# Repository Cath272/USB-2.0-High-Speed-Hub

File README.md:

# USB-2.0-High-Speed-Hub
USB 2.0 High Speed Hub with MicroSD card slot PCB designed with Kicad 8.0

Kicad Project Files, Gerber Files and STL for the case can be found in the project folders
Case uses M2X6 Screws 

# ICs

### CH334

  - USB2.0 protocol compliant 4-port USB HUB controller chip

  - Uses a 12MHz Crystal

  - 0603 100mA Fuse for limiting power to ic

  - Internal 5V to 3.3V LDO

  - Activity LED

  - [Datasheet](https://www.wch-ic.com/downloads/CH334DS1_PDF.html)

### GL823K 

  - USB 2.0 SD/MSPRO Card Reader Controller

  - Internal 5V to 3.3V LDO, can self power microSD card

  - Activity LED
  
  - [Datasheet](https://www.lcsc.com/datasheet/lcsc_datasheet_2409272232_Genesys-Logic-GL823K-HCY04_C284879.pdf)

### CH213K
  - 0.5A Low dropout ideal diode chip with current limiting function 

  - [Datasheet](https://www.wch-ic.com/downloads/CH213DS1_PDF.html)

### USBLC6
- Very low capacitance ESD protection for USB data lines

- [Datasheet](https://www.st.com/resource/en/datasheet/usblc6-2.pdf)

# Ports

### UPSTREAM

- 1 USB Type C Upstream Port (16P SMD PORT)

### DOWNSTREAM

- 2 USB TYPE C Downstream Ports (16P SMD PORT)

- 1 USB Type A Downstream Port (AF10.0 USB A, the footprint is wrong so i bent the front legs when I assambled it, to be changed) 

- 1 MicroSD card Slot (Common style size 14*15mm)

USB C ports are USB PD compliant

# Schematic

# PCB

FRONT:

BACK:

3D:

# Photos

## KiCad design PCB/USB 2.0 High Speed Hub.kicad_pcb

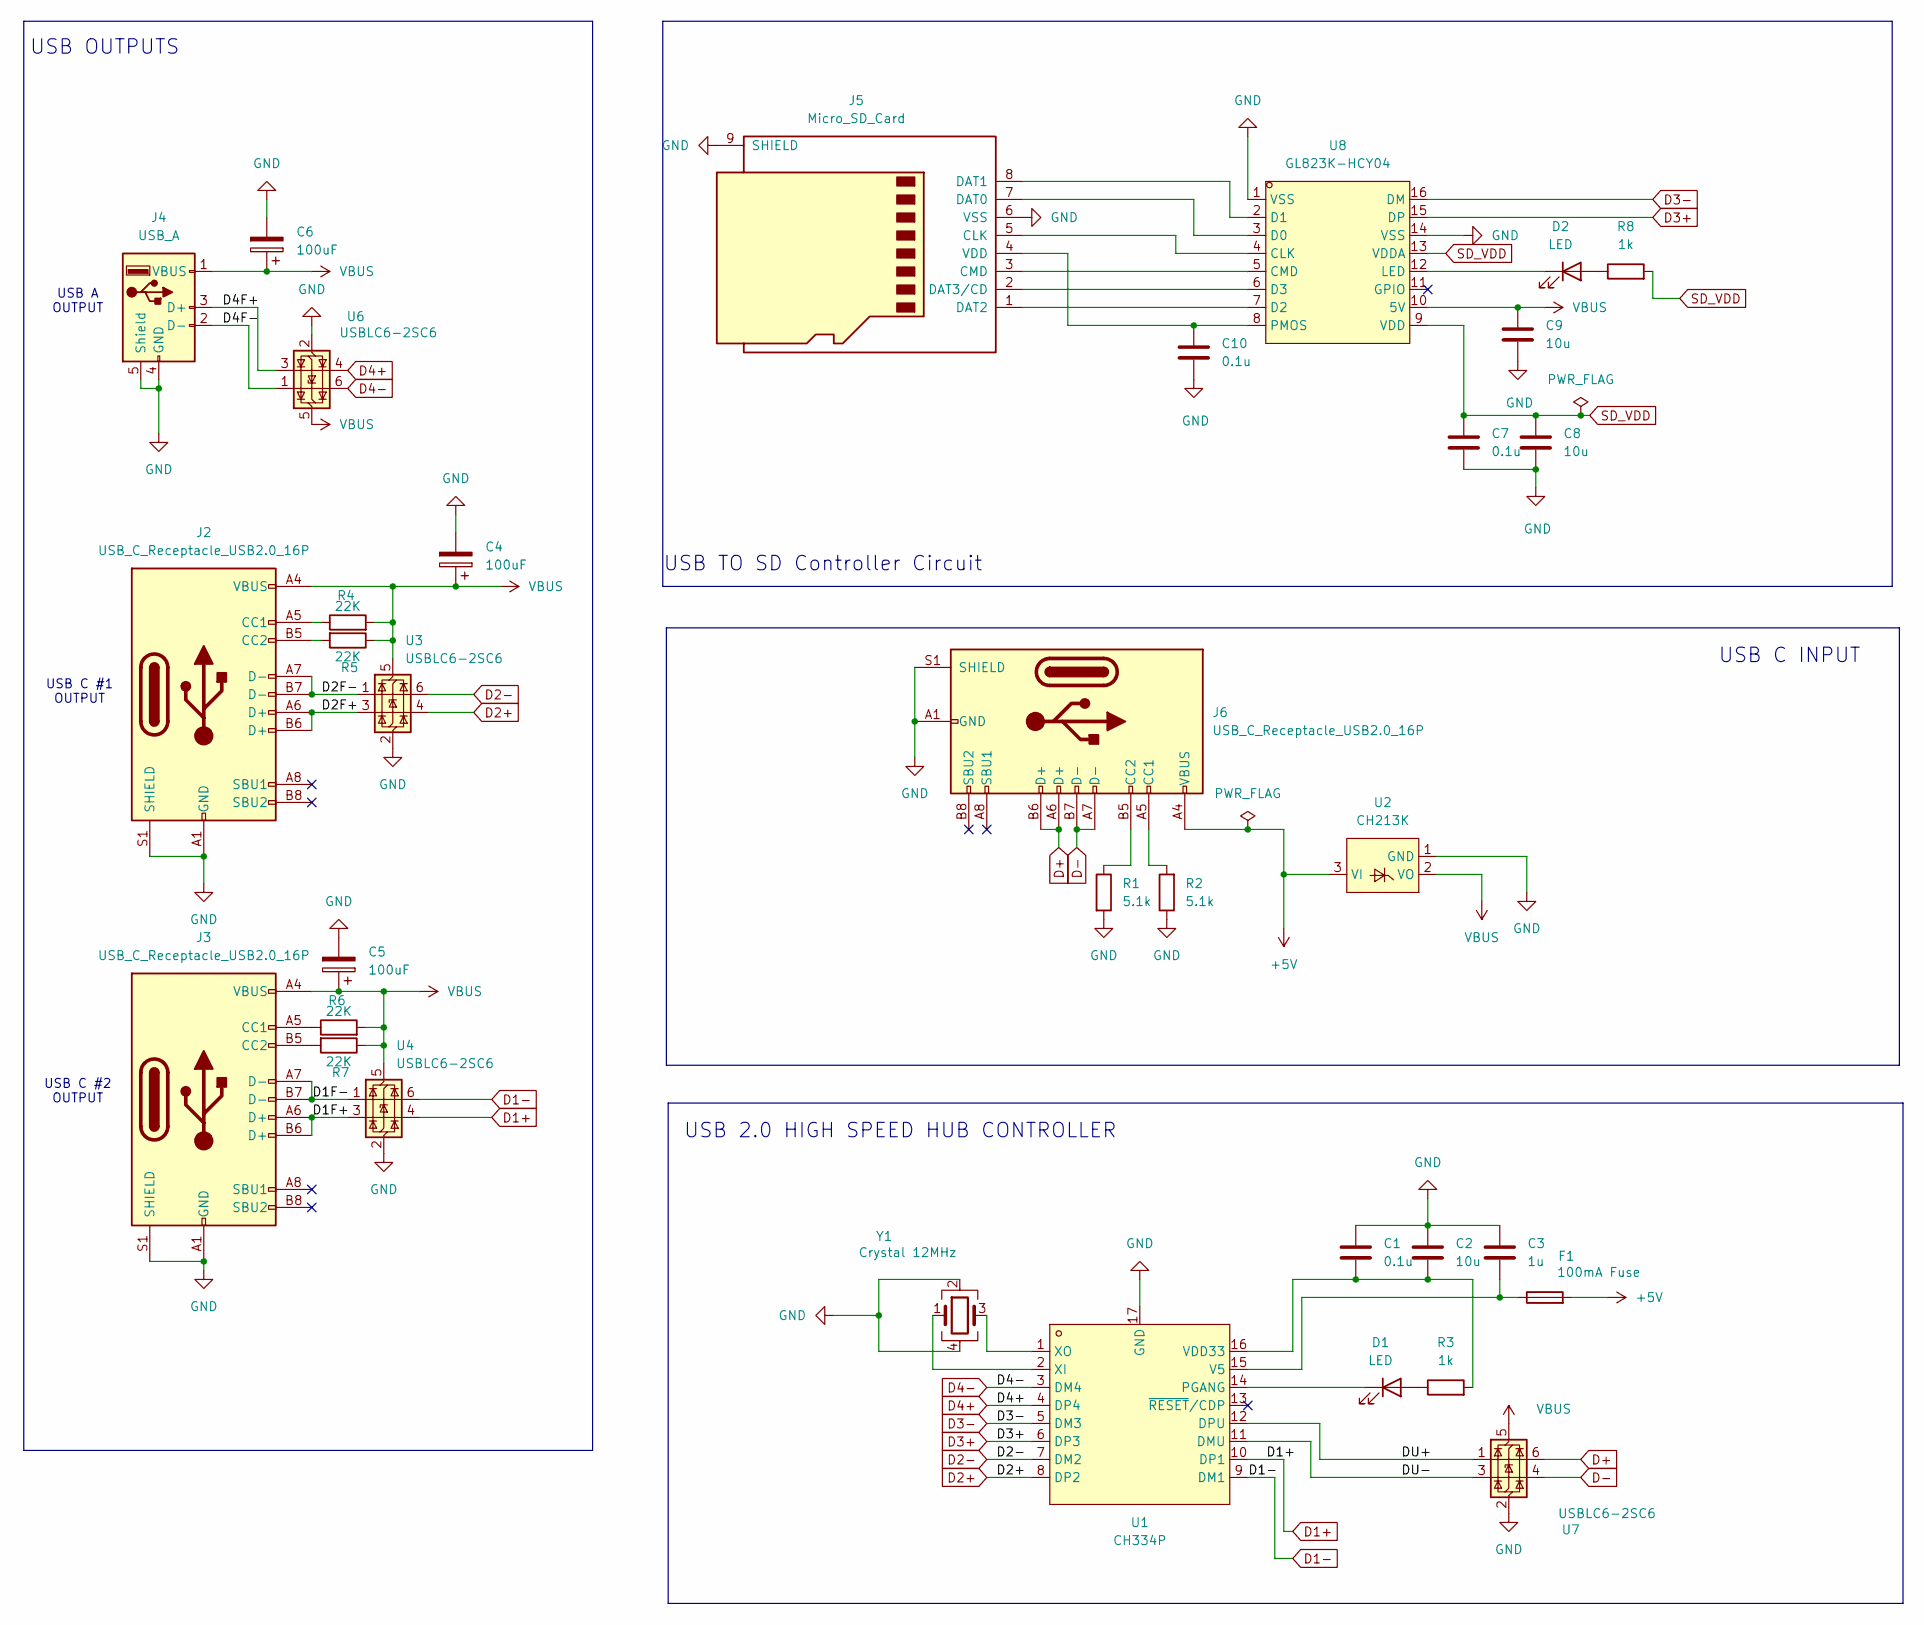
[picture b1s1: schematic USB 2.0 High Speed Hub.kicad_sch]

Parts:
C1, C7, C10: 0.1u; C_0603_1608Metric_Pad1.08x0.95mm_HandSolder
C2, C8, C9: 10u; C_0805_2012Metric_Pad1.18x1.45mm_HandSolder
C3: 1u; C_0805_2012Metric_Pad1.18x1.45mm_HandSolder
C4, C5, C6: 100uF; CP_EIA-3528-15_AVX-H_Pad1.50x2.35mm_HandSolder
D1, D2: LED; LED_0603_1608Metric_Pad1.05x0.95mm_HandSolder
F1: 100mA Fuse; Fuse_0603_1608Metric_Pad1.05x0.95mm_HandSolder
J2, J3, J6: USB_C_Receptacle_USB2.0_16P; USB_C_Receptacle_GCT_USB4105-xx-A_16P_TopMnt_Horizontal
J4: USB_A; USB-A-SMD_11.0180CB1.9
J5: Micro_SD_Card; SUNTECH_ST-TF-003A
R1, R2: 5.1k; R_0402_1005Metric_Pad0.72x0.64mm_HandSolder
R3, R8: 1k; R_0402_1005Metric_Pad0.72x0.64mm_HandSolder
R4, R5, R6, R7: 22K; R_0402_1005Metric_Pad0.72x0.64mm_HandSolder
U1: CH334P; QFN-16_L3.0-W3.0-P0.50-BL-EP1.7; LCSC Part C5373042
U2: CH213K; SOT-23
U3, U4, U6, U7: USBLC6-2SC6; SOT-23-6
U8: GL823K-HCY04; SSOP-16_L4.9-W3.9-P0.64-LS6.0-BL; LCSC Part C284879
Y1: Crystal 12MHz; Crystal_SMD_3225-4Pin_3.2x2.5mm

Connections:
+5V: F1.2, J6.A4 (VBUS), J6.A9 (VBUS), J6.B4 (VBUS), J6.B9 (VBUS), U2.3 (VI)
/D1F+: J3.A6 (D+), J3.B6 (D+), U4.3 (I/O2)
/D1F-: J3.A7 (D-), J3.B7 (D-), U4.1 (I/O1)
/D2F+: J2.A6 (D+), J2.B6 (D+), U3.3 (I/O2)
/D2F-: J2.A7 (D-), J2.B7 (D-), U3.1 (I/O1)
/D4F+: J4.3 (D+), U6.3 (I/O2)
/D4F-: J4.2 (D-), U6.1 (I/O1)
/DU+: U1.12 (DPU), U7.1 (I/O1)
/DU-: U1.11 (DMU), U7.3 (I/O2)
D1+: U1.10 (DP1), U4.4 (I/O2)
D1-: U1.9 (DM1), U4.6 (I/O1)
D2+: U1.8 (DP2), U3.4 (I/O2)
D2-: U1.7 (DM2), U3.6 (I/O1)
D3+: U1.6 (DP3), U8.15 (DP)
D3-: U1.5 (DM3), U8.16 (DM)
D4+: U1.4 (DP4), U6.4 (I/O2)
D4-: U1.3 (DM4), U6.6 (I/O1)
D+: J6.A6 (D+), J6.B6 (D+), U7.6 (I/O1)
D-: J6.A7 (D-), J6.B7 (D-), U7.4 (I/O2)
GND: C1.1, C2.1, C3.1, C4.2, C5.2, C6.2, C7.2, C8.2, C9.2, C10.2, J2.A1 (GND), J2.A12 (GND), J2.B1 (GND), J2.B12 (GND), J2.S1 (SHIELD), J3.A1 (GND), J3.A12 (GND), J3.B1 (GND), J3.B12 (GND), J3.S1 (SHIELD), J4.4 (GND), J4.5 (Shield), J5.6 (VSS), J5.9 (SHIELD), J6.A1 (GND), J6.A12 (GND), J6.B1 (GND), J6.B12 (GND), J6.S1 (SHIELD), R1.2, R2.1, U1.17 (GND), U2.1 (GND), U3.2 (GND), U4.2 (GND), U6.2 (GND), U7.2 (GND), U8.1 (VSS), U8.14 (VSS), Y1.2, Y1.4
unnamed: D1.2 (A), R3.1
unnamed: D1.1 (K), U1.14 (PGANG)
unnamed: D2.2 (A), R8.1
unnamed: D2.1 (K), U8.12 (LED)
unnamed: J2.A5 (CC1), R4.1
unnamed: J2.B5 (CC2), R5.2
unnamed: J3.A5 (CC1), R6.1
unnamed: J3.B5 (CC2), R7.2
unnamed: J5.5 (CLK), U8.4 (CLK)
unnamed: J5.3 (CMD), U8.5 (CMD)
unnamed: J5.7 (DAT0), U8.3 (D0)
unnamed: J5.8 (DAT1), U8.2 (D1)
unnamed: J5.1 (DAT2), U8.7 (D2)
unnamed: J5.2 (DAT3/CD), U8.6 (D3)
unnamed: C10.1, J5.4 (VDD), U8.8 (PMOS)
unnamed: J6.A5 (CC1), R2.2
unnamed: J6.B5 (CC2), R1.1
unnamed: C3.2, F1.1, U1.15 (V5)
unnamed: C1.2, C2.2, R3.2, U1.16 (VDD33)
unnamed: U1.2 (XI), Y1.1
unnamed: U1.1 (XO), Y1.3
SD_VDD: C7.1, C8.1, R8.2, U8.9 (VDD), U8.13 (VDDA)
VBUS: C4.1, C5.1, C6.1, C9.1, J2.A4 (VBUS), J2.A9 (VBUS), J2.B4 (VBUS), J2.B9 (VBUS), J3.A4 (VBUS), J3.A9 (VBUS), J3.B4 (VBUS), J3.B9 (VBUS), J4.1 (VBUS), R4.2, R5.1, R6.2, R7.1, U2.2 (VO), U3.5 (VBUS), U4.5 (VBUS), U6.5 (VBUS), U7.5 (VBUS), U8.10 (5V)

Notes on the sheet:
USB OUTPUTS
USB C INPUT
USB C #2 OUTPUT
USB A OUTPUT
USB C #1 OUTPUT
USB TO SD Controller Circuit
USB 2.0 HIGH SPEED HUB CONTROLLER

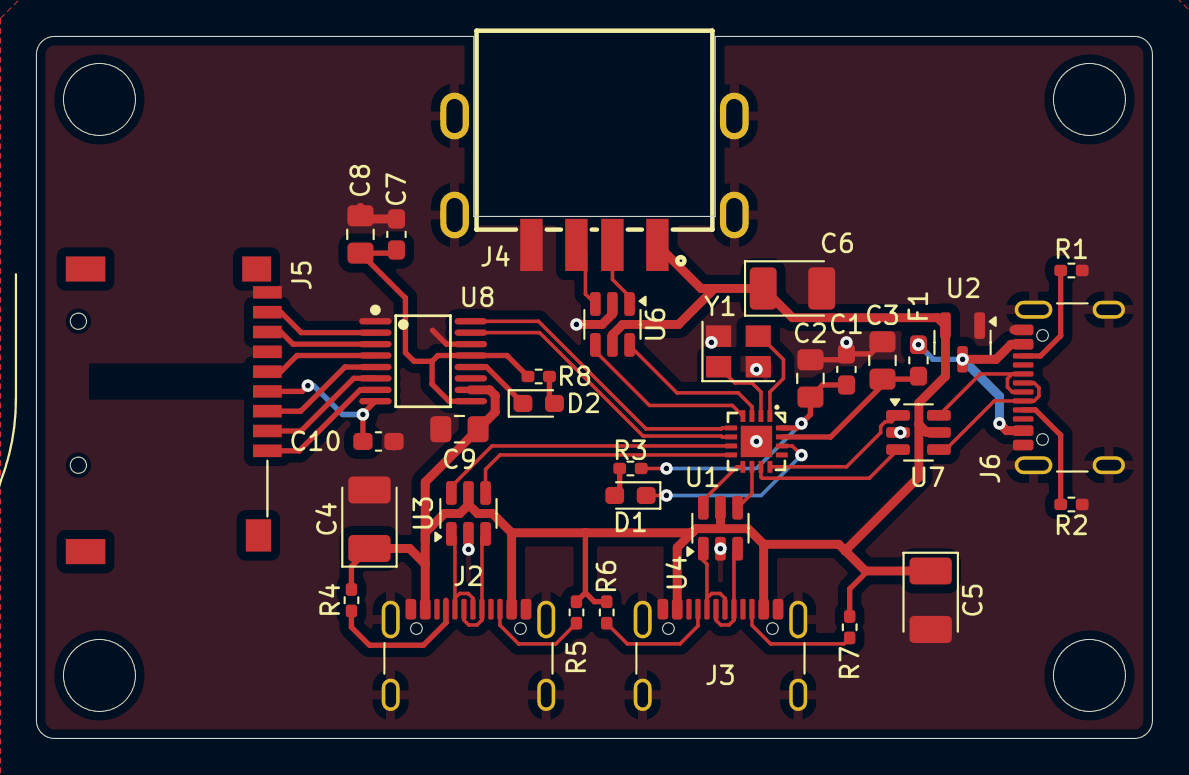
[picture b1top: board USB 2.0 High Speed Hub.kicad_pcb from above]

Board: 2 copper layers, 62.0 x 39.0 mm, 34 parts (0 on the bottom side), 43 nets.

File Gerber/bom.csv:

Designator,Footprint,Quantity,Value,LCSC Part #
"C1, C10, C7",0603,3,0.1u,
"C2, C8, C9",0805,3,10u,
C3,0805,1,1u,
"C4, C5, C6",CP_EIA-3528-15_AVX-H_Pad1.50x2.35mm_HandSolder,3,100uF,
"D1, D2",0603,2,LED,
F1,0603,1,100mA Fuse,
"J2, J3, J6",USB_C_Receptacle_GCT_USB4105-xx-A_16P_TopMnt_Horizontal,3,USB_C_Receptacle_USB2.0_16P,
J4,USB-A-SMD_11.0180CB1.9,1,USB_A,
J5,SUNTECH_ST-TF-003A,1,Micro_SD_Card,
"R1, R2",0402,2,5.1k,
"R3, R8",0402,2,1k,
"R4, R5, R6, R7",0402,4,22K,
U1,QFN-16_L3.0-W3.0-P0.50-BL-EP1.7,1,CH334P,C5373042
U2,SOT-23,1,CH213K,
"U3, U4, U6, U7",SOT-23-6,4,USBLC6-2SC6,
U8,SSOP-16_L4.9-W3.9-P0.64-LS6.0-BL,1,GL823K-HCY04,C284879
Y1,Crystal_SMD_3225-4Pin_3.2x2.5mm,1,	Crystal 12MHz,
